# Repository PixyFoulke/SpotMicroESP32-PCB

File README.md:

<!-- PROJECT LOGO -->
<br />
<div align="center">

  <h3 align="center">SpotMicroESP32-PCB</h3>

  <p align="center">
    Custom PCBs designed for SpotMicroESP32-Leika  
    <br />
    <a href="https://github.com/PixyFoulke/SpotMicroESP32-PCB/tree/main/pcbs"><strong>« Explore PCBs »</strong></a>
    <br />
    <br />
    <a href="https://github.com/pixyfoulke/SpotMicroESP32-PCB/issues/new?labels=bug&template=bug-report.md">Help</a>
    &middot;
    <a href="https://github.com/pixyfoulke/SpotMicroESP32-PCB/issues/new?labels=enhancement&template=feature-request.md">Request Variation</a>
  </p>
</div>

---
> IMPORTANT: 🛑
> AFTER TESTING, THESE BOARDS DO NOT WORK. PLEASE WAIT FOR AN UPDATE BEFORE PURCHASING. THANK YOU.

> IMPORTANT: ⚠️  
> Each ESP32 Microcontroller variant has different pin row spacing. Please select the PCB that *__will__* fit your board without stress on the pins.

> IMPORTANT: ⚠️  
> The maximum number of pins that your ESP32 can have and still use the breakout board is **40** total. If your board has more than 40, you **have** to use jumper cables to connect to the pins found on the PCB.

> IMPORTANT: ⚠️
> It is required for your board to contain *5v,3v3,SDA※,SCL※,GND*
> Futureproofed

## **- - - PCB VARIANTS - - -**
<div align="left">
    
</div>
<details>
  <summary>Expand</summary>
  
  ### **Header Pin Spacing (Open to see measurement)**
  <details>
    <summary>Expand Row Spacing Variants (Click Image To Inspect)</summary>
    <details>
      <summary>P=17mm</summary>
      
    </details>
    <details>
      <summary>P=18.5mm</summary>
      
    </details>
    <details>
      <summary>P=20mm</summary>
      
    </details>
    <details>
      <summary>P=21mm</summary>
      
    </details>
    <details>
      <summary>P=22mm</summary>
      
    </details>
    <details>
      <summary>P=23mm</summary>
      
    </details>
  </details>
</details>

---

## **- - - HARDWARE - - -**
<div align="left">
    
</div>
<details>
  <summary>Expand</summary>

  _This PCB layout is specifically designed for SpotMicroESP32-Leika._
</details>

---

## **- - - GETTING STARTED - - -**
<div align="left">
    
</div>
<details>
  <summary>Expand</summary>
  
  > IMPORTANT: ⚠️  
  > **SOLDERING IRON REQUIRED!**  
  > You will need to **manually solder** some components onto the PCB.

  ### **Setup Instructions**
  1. **📥 Download Gerber Files:**  
  - Available in the [PCBs directory](https://github.com/pixyfoulke/SpotMicroESP32-PCB/tree/master/pcbs).
    
  2. **🔩 Create BOM**  
     - Once you have selected the PCB variant, there is a folder called "/parts/". Edit the ".csv" file to fit the format of your selected manufacturer.

  3. **🛒 Order PCB:**  
     - Upload Gerber files to a PCB manufacturer (e.g., [JLCPCB](https://jlcpcb.com/)).  

  4. **🔧 Assemble PCB:**  
     - Solder components as per the schematic.  

  5. **🖇️ Connect Components:**  
     - Refer to the **[SpotMicroESP32-Leika](https://github.com/runeharlyk/SpotMicroESP32-Leika)** documentation.  

  6. **🔌 Upload Firmware:**  
     - Flash the **ESP32 microcontroller** with the SpotMicroESP32-Leika firmware.  
</details>

---

## **- - - MIT LICENSE - - -**
<div align="left">
    
</div>
<details>
  <summary>Expand</summary>

  This project is licensed under the **MIT License**. See [LICENSE](https://github.com/pixyfoulke/SpotMicroESP32-PCB/blob/master/license) for details.  
</details>

---

## **- - - ACKNOWLEDGEMENTS - - -**
<div align="left">
    
</div>
<details>
  <summary>Expand</summary>

  **Special thanks to:**

  - **Rune Harlyk** – Creator of **SpotMicroESP32-Leika**  

  - **SpotMicroAI Community** – [Join the Discord](https://discord.gg/WwefSZczQA)  
</details>

---

## **- - - HELP SERVICES - - -**
<div align="left">
    
</div>
<details>
  <summary>Expand</summary>

  👋 Contact Us!

  - **PixyFoulke** – PCB design & assembly inquiries; Discord Username: "_pixy."

  - **Rune Harlyk** – [GitHub Discussions](https://github.com/runeharlyk/SpotMicroESP32-Leika/discussions)  

  - **SpotMicroAI Community** – [Join Discord](https://discord.gg/WwefSZczQA)
    <details>
    <summary>FAQ</summary>
      
      Q: Who are you?
      
      A: Hi! I'm Jaxlyn or "PixyFoulke", I'm a 17 year old highschool aerospace engineering intern from Columbus, Ohio. I've been studying all aspects of engineering since before I could speak. I use 

    Q: How much does the PCB cost?

    A: Depends on the cost of the parts, but for me (JLCPCB), $60. If the cost is too high and you're younger than 19, check out [OnBoard](https://github.com/hackclub/OnBoard)

    Q: Why?

    A: I made this PCB after a failed hackathon attempt. Due to the small space, and the high density of wires used, there was a very high likelyhood of wires shorting, and smoke (this happened a LOT).

    Q: Will any ESP32 work?
    
    A: Yes. As long as the board has SDA and SCL pin(s), it will work. If your board has 18 pins, or 22 pins (up to 40 total pins), it will work. But you will have empty unused pins (which is completely fine).
    
    Q: How do I edit the PCB files?
    
    A: Download and Install KiCAD, open your specific PCB project (found in /pcbs/{selected_spacing}/). Here's basic learning resources for beginners: [Here](https://learn.sparkfun.com/tutorials/beginners-guide-to-kicad)
    
    Q: Can you do it for me?
    
    A: Two answers yes (see below) and no. If you need help with the PCB, DM PixyFoulke (see above). If you need help with Leika, open a GitHub Discussion [here](https://github.com/runeharlyk/SpotMicroESP32-Leika/discussions). After making edits/fixes, feel free to open a PR to have it added to this repository!  

    > **Important ⚠️**  
    > If you want me (PixyFoulke) to assemble the PCB and ship it to you, you will have to pay an **$80 deposit upfront**. Once it's in transit, you **must** pay the remaining balance.  
    > If you fail to pay within 48 hours (some exceptions may apply, but must be communicated via email), the **$80 deposit is non-refundable** for damages and losses.  

    A #2: Yes, if you live in North America, I (PixyFoulke) can order, assemble, and deliver the completed and tested PCB for you. However, you will need to cover all costs, including PCB manufacturing, parts, assembly, and shipping.  

    **Full Cost Breakdown:**  
    - **PCB cost:** ~$70  
    - **Labor cost (Soldering components):** ~$20  
    - **Part cost:**  
      - [PCA9685](https://a.co/d/jlCFAqK)  
      - [MPU6050](https://a.co/d/4rnn9Vi)  
    - **(Optional) Personalized 3D-Printed Mounting Plate** ($5) *(Files in `/pcbs/` folder)*  
    - **Shipping Cost:** TBD (You must pay this ahead of time)  

    **Subtotal:** $120 + Shipping + (Optional: Personalized Mounting Plate)  

    Q: How do I connect the pins?
    
    A: Use short jumper wires (Female-To-Male dupont) to connect the exposed male header pins to the exposed 
    
    </details>
</details>

--- 
🎯 **Want to contribute?** Fork the repo, submit PRs, and help improve the project!

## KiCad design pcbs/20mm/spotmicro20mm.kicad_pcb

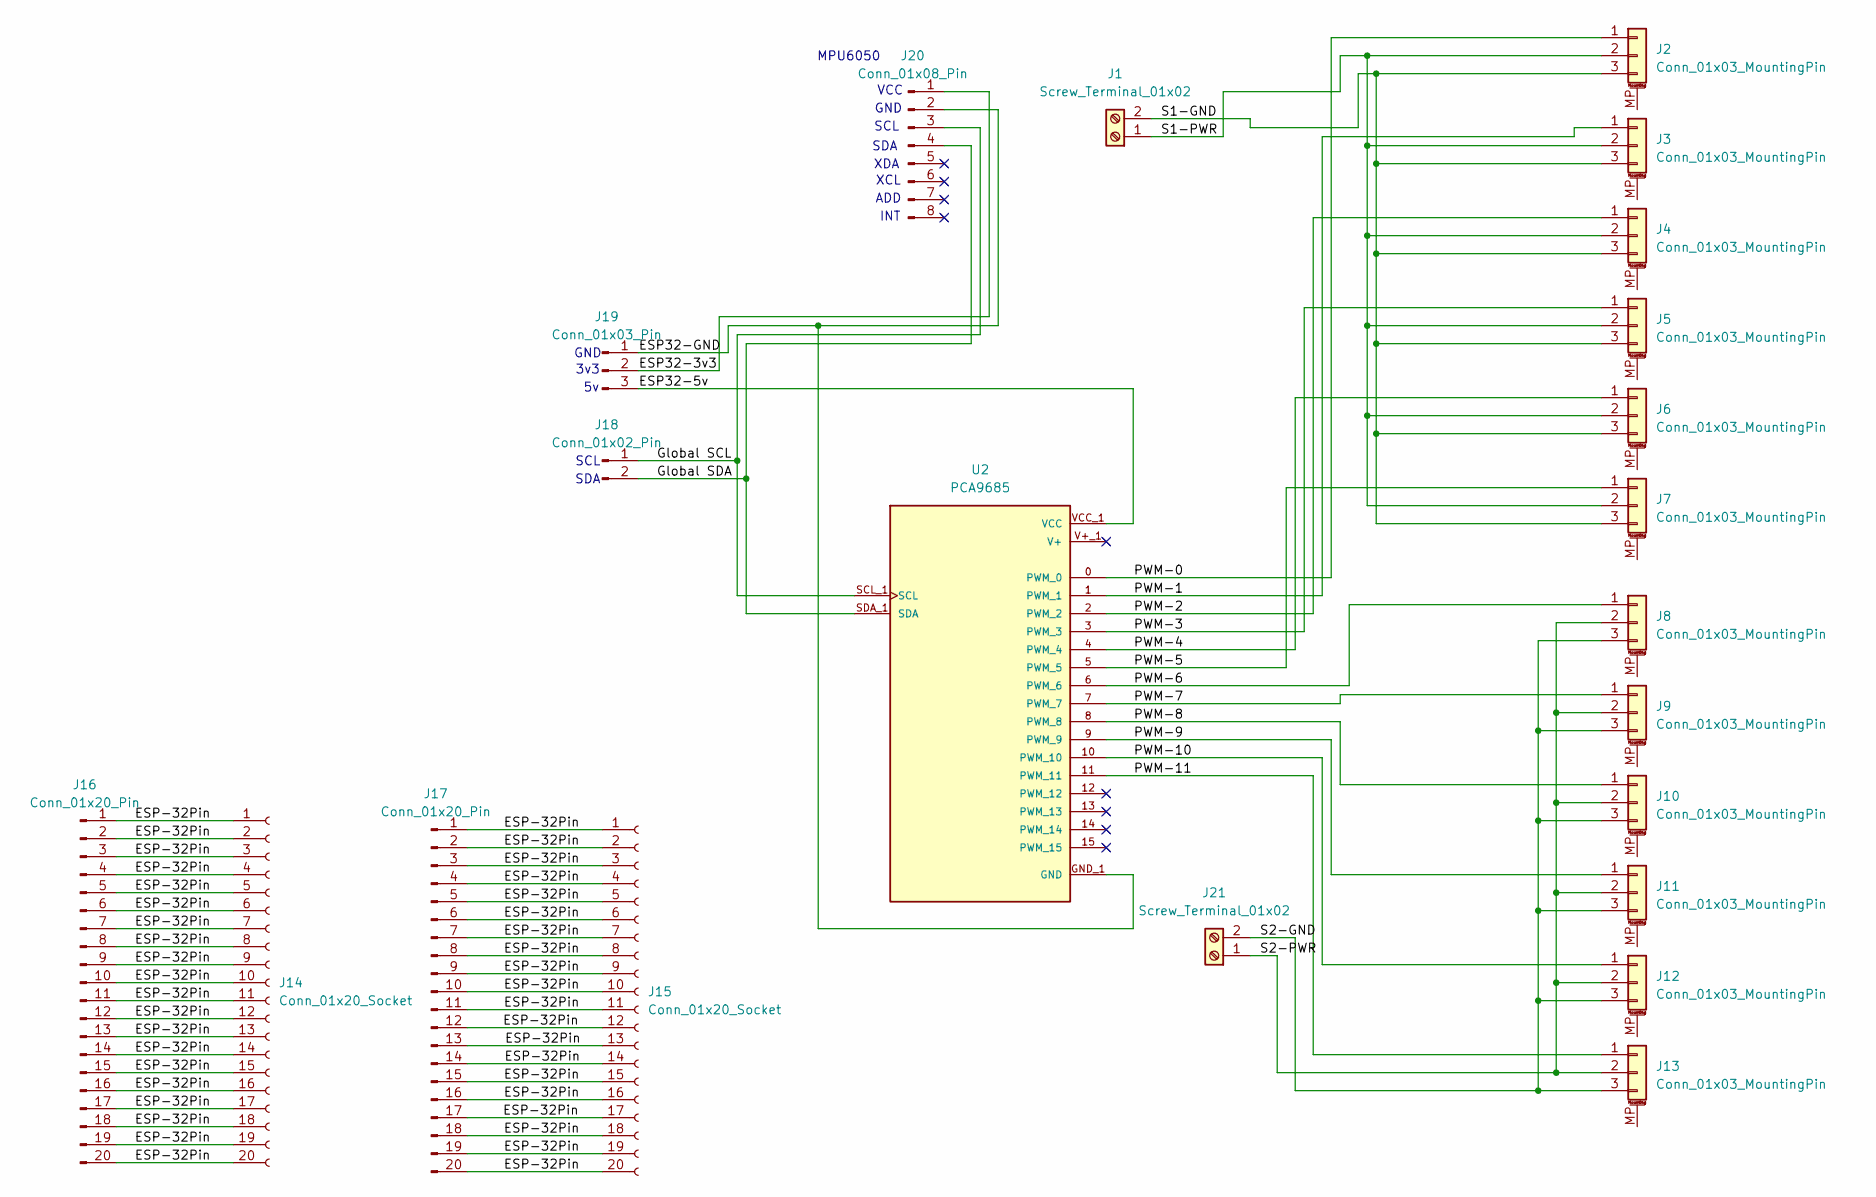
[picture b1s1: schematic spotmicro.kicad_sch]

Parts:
J1, J21: Screw_Terminal_01x02; TerminalBlock_Phoenix_MKDS-1,5-2_1x02_P5.00mm_Horizontal
J2, J3, J4, J5, J6, J7, J8, J9, J10, J11, J12, J13: Conn_01x03_MountingPin; PinHeader_1x03_P2.54mm_Vertical
J14, J15: Conn_01x20_Socket; PinSocket_1x20_P2.54mm_Vertical
J16, J17: Conn_01x20_Pin; PinHeader_1x20_P2.54mm_Vertical
J18: Conn_01x02_Pin; PinSocket_1x02_P2.54mm_Vertical
J19: Conn_01x03_Pin; PinSocket_1x03_P2.54mm_Vertical
J20: Conn_01x08_Pin; PinSocket_1x08_P2.54mm_Vertical
U2: PCA9685; MODULE_815; PARTREV C

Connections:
/ESP32-3v3: J19.2, J20.1
/ESP32-5v: J19.3, U2.VCC_1 (VCC)
/ESP32-GND: J19.1, J20.2, U2.GND_1 (GND)
/ESP-32Pin: J14.1, J14.2, J14.3, J14.4, J14.5, J14.6, J14.7, J14.8, J14.9, J14.10, J14.11, J14.12, J14.13, J14.14, J14.15, J14.16, J14.17, J14.18, J14.19, J14.20, J15.1, J15.2, J15.3, J15.4, J15.5, J15.6, J15.7, J15.8, J15.9, J15.10, J15.11, J15.12, J15.13, J15.14, J15.15, J15.16, J15.17, J15.18, J15.19, J15.20, J16.1, J16.2, J16.3, J16.4, J16.5, J16.6, J16.7, J16.8, J16.9, J16.10, J16.11, J16.12, J16.13, J16.14, J16.15, J16.16, J16.17, J16.18, J16.19, J16.20, J17.1, J17.2, J17.3, J17.4, J17.5, J17.6, J17.7, J17.8, J17.9, J17.10, J17.11, J17.12, J17.13, J17.14, J17.15, J17.16, J17.17, J17.18, J17.19, J17.20
/Global SCL: J18.1, J20.3, U2.SCL_1 (SCL)
/Global SDA: J18.2, J20.4, U2.SDA_1 (SDA)
/PWM-0: J2.1, U2.0 (PWM_0)
/PWM-1: J3.1, U2.1 (PWM_1)
/PWM-2: J4.1, U2.2 (PWM_2)
/PWM-3: J5.1, U2.3 (PWM_3)
/PWM-4: J6.1, U2.4 (PWM_4)
/PWM-5: J7.1, U2.5 (PWM_5)
/PWM-6: J8.1, U2.6 (PWM_6)
/PWM-7: J9.1, U2.7 (PWM_7)
/PWM-8: J10.1, U2.8 (PWM_8)
/PWM-9: J11.1, U2.9 (PWM_9)
/PWM-10: J12.1, U2.10 (PWM_10)
/PWM-11: J13.1, U2.11 (PWM_11)
/S1-GND: J1.2, J2.3, J3.3, J4.3, J5.3, J6.3, J7.3
/S1-PWR: J1.1, J2.2, J3.2, J4.2, J5.2, J6.2, J7.2
/S2-GND: J8.3, J9.3, J10.3, J11.3, J12.3, J13.3, J21.2
/S2-PWR: J8.2, J9.2, J10.2, J11.2, J12.2, J13.2, J21.1

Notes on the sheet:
SDA
GND
XCL
MPU6050
VCC
INT
SCL
3v3
XDA
ADD

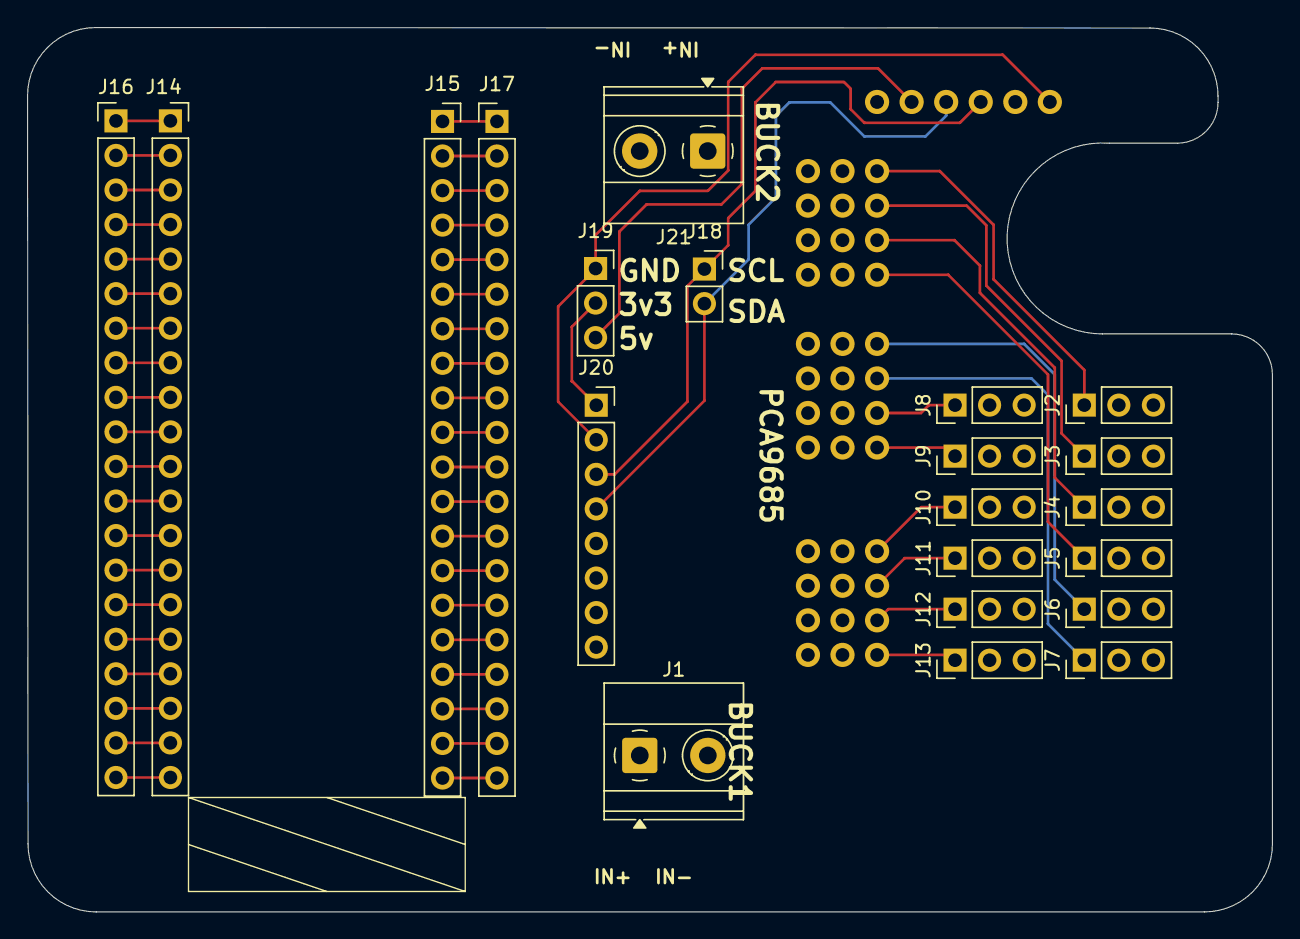
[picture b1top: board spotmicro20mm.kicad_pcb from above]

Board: 4 copper layers, 91.5 x 65.0 mm, 22 parts (0 on the bottom side), 22 nets.

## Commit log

2025-03-26 Create images folder
2025-03-26 add base images
2025-03-26 🪐Beginning PCB Upload Process
    Gerbers and Parts coming to a theater near you soon
2025-03-26 fixed readme and added license (MIT)
2025-03-26 Added Gerbers and Other Files
2025-03-27 ⭐fix
2025-03-27 Added more documentation and FAQ
2025-03-27 Image Fix
2025-03-27 another bites the dust - image fix #2
    Last commit made the dogs stretchy
2025-03-28 Fixed conflicting names
2025-03-28 Gerbers.zip added
2025-04-16 Add warning to README.md
    PCBs do not work. Will fix once I'm not stuck in a rut
